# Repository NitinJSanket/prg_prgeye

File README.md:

# prg_prgeye
Tri-camera module with IMU and dual/triple Cortex M7

## Code Structure

```
Software
└── DeepLearning 
    ├── HomographyNetUnsup
    |   └── *
    ├── RealData
    |   └── *
    ├── SimilarityNet
    |   └── *
    ├── SuperPoint
    |   └── *
    └── SpeedTests
        └── *
```

- `HomographyNetUnsup` has the depracated code from EVDodgeNet.
- `RealData` has the code for evaluation on data from simulation and real world.
- `SimilarityNet` has the code for training and evaluation for all the scenarios presented in the paper.
- `SpeedTests` has the code for testing speed of various networks.

### `SimilarityNet`
To train use `TrainSimilarityNet.py`. The following command line flags can be used.
- `--BasePath`: Base path from where images are loaded, eg., /home/nitin/Datasets/MSCOCO/train2014Processed.
- `--NumEpochs`: Number of epochs the training will be done for
- `--DivTrain`: Factor to reduce Train data by per epoch, used for debugging only or for super large datasets.
- `--MiniBatchSize`: Size of the MiniBatch to use.
- `--LoadCheckPoint`: Load Model from latest Checkpoint from CheckPointPath?
- `--RemoveLogs`: Delete log Files from ./Logs? (BUGGY, DON'T USE).
- `--LossFuncName`: Choice of Loss functions, choose from SL2 (Supervised L2 loss), PhotoL1 (Photometric L1), PhotoChab (Photometric Chabonnier), SSIM (SSIM Loss from GeoNet), SSIMTF (TF's Implementation of GeoNet's SSIM loss). Any loss can be suffixed with HP or SP to compute loss on Highpassed image or SuperPoint cornerness respectively.
- `--RegFuncName`: Choice of regularization function, choose from None, SP (Cornerness from SuperPoint) or HP (Highpassed image). Total loss is computed as LossFunc + sum(Alpha_i * RegFunc_i)
- `--NetworkType`: Choice of Network type, choose from Small, Large.
- `--NetworkName`: Name of network file, eg., Network.VanillaNet. Change the line `VN = Net.xxx` in  `TrainOperation` function to use the correct class name of the network.
- `--CheckPointPath`: Path to save checkpoints.
- `--LogsPath`: Path to save Logs.
- `--GPUDevice`: What GPU do you want to use? -1 for CPU.
- `--DataAug`: Depracated, DO NOT USE. Instead Augment data before and create a dataset.
- `--LR`: Learning Rate.
- `--InitNeurons`: Number of Neurons in the first layer
- `--Input`: Input, choose from I: RGB Images, G: Grayscale Images, HP: HP Grayscale Images, SP: Cornerness from SuperPoint.

## `SpeedTests`
To run the code use `CreateNetwork.py`. The following command line flags can be used.
- `--CheckPointPath`: Path to save Model, eg., /home/nitin/PRGEye/CheckPoints/SpeedTests
- `--ModelPrefix`: Prefix for model name, Useful if you are running for different variants of the model.
- `--GPUDevice`: What GPU do you want to use? -1 for CPU
- `--MiniBatchSize`: Size of the MiniBatch to use
- `--NetworkName`: Name of network file, eg., Network.VanillaNet
- `--TestMultipleMiniBatch`: Used for Testing only, Test for running at different batch sizes. If active MiniBatchSize represents max value.
- `--NumTest`: Number of times code will run to take Avg. time.
- `--Mode`: Train creates the Model. Test runs the speed tests. Don't use TrainTest mode.
- `--MiniBatchMin`: Used for Testing only, is active when TestMultipleMiniBatch is used and MiniBatchMin represents min value.
- `--MiniBatchSizeIncrement`: Used for Testing only, is active when TestMultipleMiniBatch is used and MiniBatchSize represents max value. The code is tested for these increment steps.
- `--ForceBatchSize1`: Used for Testing only, is active when TestMultipleMiniBatch is used and MiniBatchSize represents max value. Force runs for BatchSize of 1.
- `--TFLite`: Convert to TFLite quantized to type --TFLiteQuant? 
- `--TFLiteOpt`: TFLite Optimization, Choose from Default, Size and Latency.
- `--TFLiteQuant`: TFLite Quantization. Choose from Float32, Float16, Int64, Int32, Int8, UInt8. Default: Float32
- `--EdgeTPU`: TFLite For EdgeTPU. This works in addition to TFLite conversion.
- `--InitNeurons`: Number of Neurons in the first layer

**Additional Notes:**
- Use TF 1.15 in Python 2.7 for Train mode in `SpeedTests`.
- Use TF 1.14 in Python 3.6.9 for Test mode in `SpeedTests`.
    
## References for Images
- [Benchmark Analysis of Representative Deep Neural Network Architectures](https://arxiv.org/abs/1810.00736)
- [An Analysis Of Deep Neural Network Models For Practical Applications](https://arxiv.org/abs/1605.07678)

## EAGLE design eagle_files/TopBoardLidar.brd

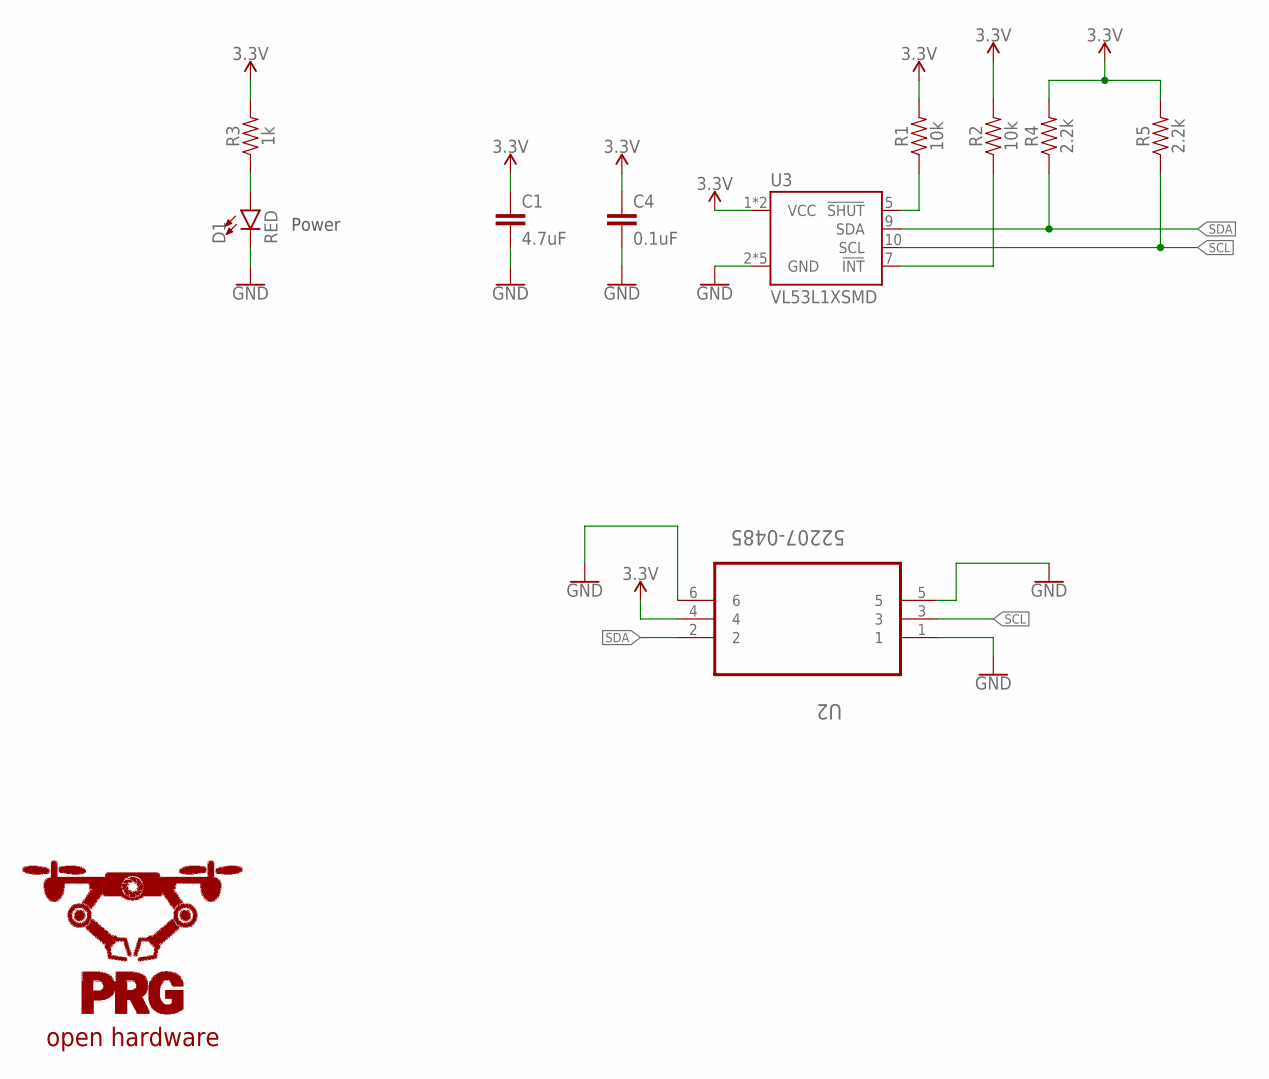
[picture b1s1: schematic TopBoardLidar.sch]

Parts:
C1: 4.7uF; 0603
C4: 0.1uF; 0603
D1: RED; LED-0603
R1, R2: 10k; 0603
R3: 1k; 0603
R4, R5: 2.2k; 0402-TIGHT
U2: 52207-0485; MOLEX_52207-0485
U3: VL53L1XSMD; VL53L1X

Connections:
3.3V: C1.1, C4.1, R1.2, R2.2, R3.2, R4.2, R5.2, U2.4, U3.1 (VCC), U3.11 (VCC)
GND: C1.2, C4.2, D1.C, U2.1, U2.5, U2.6, U3.2 (GND), U3.3 (GND), U3.4 (GND), U3.6 (GND), U3.12 (GND)
unnamed: R1.1, U3.5 (!SHUT)
unnamed: D1.A, R3.1
unnamed: R2.1, U3.7 (!INT)
SCL: R5.1, U2.3, U3.10 (SCL)
SDA: R4.1, U2.2, U3.9 (SDA)

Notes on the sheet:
Power
open hardware

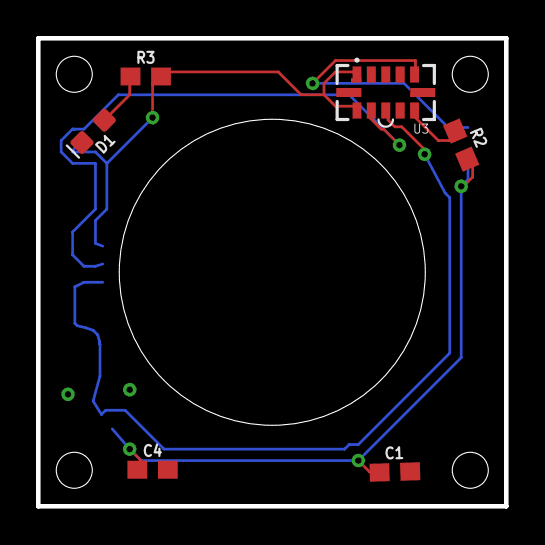
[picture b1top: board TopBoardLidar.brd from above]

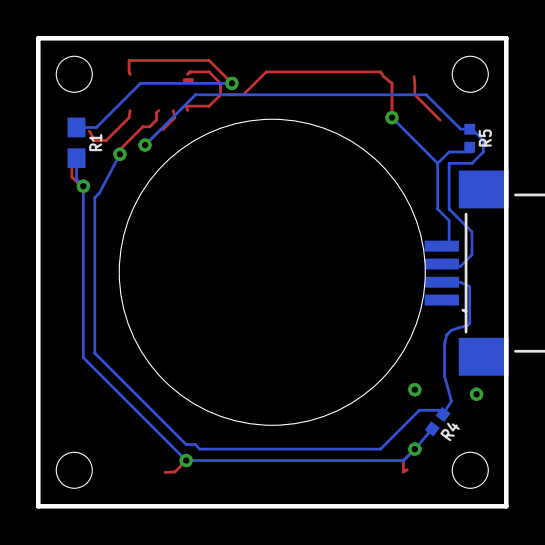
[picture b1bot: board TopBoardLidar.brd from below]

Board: 4 copper layers, 26.0 x 26.0 mm, 10 parts (4 on the bottom side), 7 nets.

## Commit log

2018-10-11 Added breakout boards and price
    for VL53L0X, STM32H743VIH6, ICM-20789
2018-10-11 Add link to the camera module
2018-10-11 Corrected row NOIP1SN1300A
2018-10-14 Add breakout board link for VL53L1X
2019-04-12 micropython test code for IMU
2019-04-13 added pin connection images
2019-07-06 Tested IMU9250 with Arduino Micro
2019-07-06 Tested IMU9250 with Arduino Microv2
2019-07-06 Tested with Arduino Micro
2019-07-07 Added Homography Code: Under Progress
2019-07-10 Modified Test Code
2019-07-11 added tested arduino code for time of flight sensors
2019-07-15 Updated TrainHomographyHP
2019-07-15 Updated HP Code
2019-07-16 changed VL53l1x library to run at ~500hz
2019-07-17 Completed IMU LIDAR code
2019-07-17 made sensible topic name
2019-07-18 added VL53L1x eagle library
2019-07-18 added sparkfun library
2019-07-18 added imu MPU9250
2019-07-19 added support for teensy
2019-07-19 added images
2019-07-19 Rename README.md to README-arduino.md
2019-07-19 completed top board; started bottom borad
2019-07-20 completed bottom layer.. and started with nanopi shield
2019-07-20 Added No Rot
2019-07-21 added few libraries and completed all schematic
2019-07-21 deleted bottomboard_imu file
2019-07-21 updated nanopi shield
2019-07-21 added molex for cam
2019-07-23 renamed folder
2019-07-31 top layer board routing
2019-08-07 Added IC-STN test code
2019-08-09 Updated ICSTN
2019-08-12 Updated ICSTN code
2019-09-23 Updated ICSTN Code, works I guess
2019-10-01 Updated ICSTN Homography code with Chabonnier loss
2019-10-10 modified arduino-serial
2019-10-31 Adding RunICSTN Code
2019-11-07 Updated ICSTN codes
2019-11-26 Update RunICSTN
2020-01-03 Added SuperPoint Code
2020-01-07 Modified Superpoint
2020-01-07 Added Working SuperPoint Training Code
2020-01-09 Updated RunHomographyNetICSTN with plotting functions
2020-01-09 Updated ICSTN Run code with Error calculation
2020-01-09 test update
2020-01-09 Test2
2020-01-13 Updated ImageUtils
2020-01-13 Updated TestWarpRot to test class functions
2020-01-13 Fixed bugs in Homography waerping
2020-01-14 Updated ICTSNSimpler Code and ICTSN warp list hadnling
2020-01-14 Fixed bugs in updated ICSTN code
2020-01-14 Updated ICSTNSimpler
2020-01-14 Modified RunHomographyNet (commented out)
2020-01-14 Added MatToHDF5 Converter
2020-01-15 Updated warpICSTN to include scale and yaw
2020-01-15 Updated superpoint weights
2020-01-15 Wroking Yaw and Scale transformations
2020-01-15 Added Number of parameters counting in SuperPointNet code
2020-01-19 Added ComposeReducedH
2020-01-22 Fixed bugs in HomographyClass
2020-01-22 Fixed bugs in Homography class RandTranslation
2020-01-22 Updated TestHomographyClass
2020-01-23 Added SpeedTest codes
2020-01-25 Added SimilarityNet code
2020-01-25 Updated warpICSTN2
2020-01-26 Added Warping code using Numpy
2020-01-27 Added New HomographyICSTN Class
2020-01-28 Revamped BatchCreation to use TF along with new class
2020-01-29 Added Base Class for creating model with autonaming
2020-01-29 Completed SqueezeNet
2020-01-29 Moved Decorators to new file
2020-01-29 Added DenseNet v0.1
2020-01-30 Bug fixes with Decorator imports
2020-01-30 Updated TODO
2020-01-30 Fixed bug in Squeezenet so it can run
2020-01-30 Updated SqueezeNet to not run as module
2020-01-30 Modified Readme
2020-01-30 Updated SpeedTests to include Model size computation
2020-01-31 Fixed bug in ImageUtils cropping
2020-01-31 Added Evaluation and Plotting Code
2020-02-01 Added Code for VanillaNet
2020-02-01 Fixed bug in VanillaNet
2020-02-02 Fixed bugs in VanillaNet
2020-02-02 Updated Readme with Refs
2020-02-02 Variations of VanillaNet
2020-02-02 Added SqueezeNet
2020-02-02 Fixed bug in SqueezeNet
2020-02-02 Aborted DenseNet
2020-02-02 Added ResNet
2020-02-02 Fixed bugs in ResNet
2020-02-03 Cleaned up code
2020-02-03 Fixed major bugs in ImageUtils and cleaned TrainSimilarityNet
2020-02-03 Modified default Training params
2020-02-03 Modified TrainSimilarityNet
2020-02-04 Updated VanillaNet
2020-02-04 Updated SpeedTest
2020-02-04 Updated VaniilaNet Params
2020-02-04 Added MobileNetv1 and ShuffleNetv2
2020-02-05 Updated Evaluation Code
2020-02-05 Added Scaling to different parts of loss
2020-02-05 Modified Files for scale + translation
2020-02-06 Fixed bug in VanillaNet2 (scale + translation)
2020-02-06 Fixed bug in warpICTSN2 (scale)
2020-02-06 Fixed bug in Ideal Image Warp
2020-02-07 Added VanillaNet3 for 2t2s training
2020-02-07 Added Notes
2020-02-08 Modified Evaluation code
2020-02-08 Added logging on exit
2020-02-08 Added losses to TrainSimilarityNet
2020-02-09 Modified Notes
2020-02-10 Modified Train code
2020-02-10 Updated VanillaNet for 2 PS
2020-02-11 Updated Network Config
2020-02-11 Updated NetworkConfig
2020-02-13 Added VanillaNet2Simpler for scale x 1 + translation x 1
2020-02-13 Added VanillaNet3Simpler for trans x 1 + scale x 1
2020-02-14 Added TFLite code in SpeedTests
2020-02-14 Fixed ResNet3 bugs
2020-02-14 Added DiffOverlay display on TensorBoard
2020-02-16 Fixed bug in ResNet3
2020-02-17 Restructure folders
2020-02-17 Added SqueezeNet3
2020-02-18 Fixed bug in MobileNetv1 and MobileNetv13
2020-02-18 Fixed bugs in ShuffleNetv2 and ShuffleNetv23
2020-02-18 Modified NetworkConfig
2020-02-18 Updated NetworkConfig.md
2020-02-18 Run ShuffleNetv23
2020-02-18 Update RunCommand
2020-02-23 Test update Notes
2020-02-23 Test update Notes 2
2020-02-23 Updated Notes
2020-02-23 Updated RunCommand
2020-02-23 Added TF to TFLite converter
2020-02-23 Updated MobileNetv1TFLite
2020-02-23 Updated TFLite
2020-02-24 Update RunCommnd
2020-02-24 Updated NeyworkConfig
2020-02-24 Added PhotoL1 and PhotoChab losses
2020-02-24 Fixed bugs in PhotoL1 and PhotoChab
2020-02-28 Fixed bugs in TrainSimilarityNet
2020-03-02 Added HP Loss
2020-03-06 Added SSIM loss
2020-03-06 Added New Folder for testing on blender and real data
2020-03-11 Added ResAndSqeeNet training together for 1PS
2020-03-11 Fixed Bug in ResAndSqueezeNet
2020-03-11 Update RunCommand with half Size ResNet Model (11.646MB)
2020-03-15 Added SuperPoint Training Code
2020-03-16 Added Input funcitonality
2020-03-16 Added DataAugmentationNP Class
2020-03-16 Fixed bug in SuperPoint Regularization
2020-03-16 Updated TensorRT Network
2020-03-17 Updated Readme' '
2020-03-17 Added DataAugmentationTF class
2020-03-19 Parse Diff Loss Function Suffixes
2020-03-20 Fixed Bugs in Gray Scale
2020-03-21 Fixed Bug in TrainSImilarityNet copy of opt
2020-03-21 Fixed Bug in BatchCreation when using HP input
2020-03-22 Updated Decorator to take suffix
2020-03-23 Added Evaulatuin For Only T
2020-03-23 Bug Fix in HP Reg
2020-03-24 Updated DataAug
2020-03-25 Added Reg Func for SP and HP
2020-03-26 Major rebase of SpeedTests and Python3 Support
2020-03-26 Added TFMatMulTest
2020-03-27 Bug Fixes in SpeedTests TFLite conversions
2020-03-27 Added Common Bugs
2020-03-27 Added TFLite SpeedTests
2020-03-28 Added Small Models in SpeedTests
2020-03-29 Fixed bug in SpeedTests Test supporting TFLiteQuant
2020-03-29 Teacher Student Code
2020-03-29 Bug fixes in ModelDistillation
2020-03-30 Updated Distillation
2020-03-30 Added Evaluation code for Distillation
2020-03-31 Bug fixes in Evaluation of Distillation
2020-03-31 Added Suffix to TrainSimilarityNet
2020-04-03 Bug fixes in Distillation TS
2020-04-06 Added SpeedTests Visualization
2020-04-06 Updated Plot
2020-04-07 Updated TestPlot
2020-04-07 Added functionality to CreateNetwork
2020-04-14 Added functionality to Evaluation code
2020-04-14 Updated Eval code
2020-04-21 Updated RealData to output csv
2020-04-21 Cleanup Plotting folder
2020-04-25 Added SkipNum Flag to EvaluateSimilarityNet in Real Data
2020-04-25 Added Corel files
2020-04-26 Fixed errors in excel file
2020-04-29 Added Trajectory Plots
2020-05-01 Added Vid2Frames

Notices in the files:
parts and their libraries:
SparkFun-Capacitors: Licensing: Creative Commons ShareAlike 4.0 International - https://creativecommons.org/licenses/by-sa/4.0
